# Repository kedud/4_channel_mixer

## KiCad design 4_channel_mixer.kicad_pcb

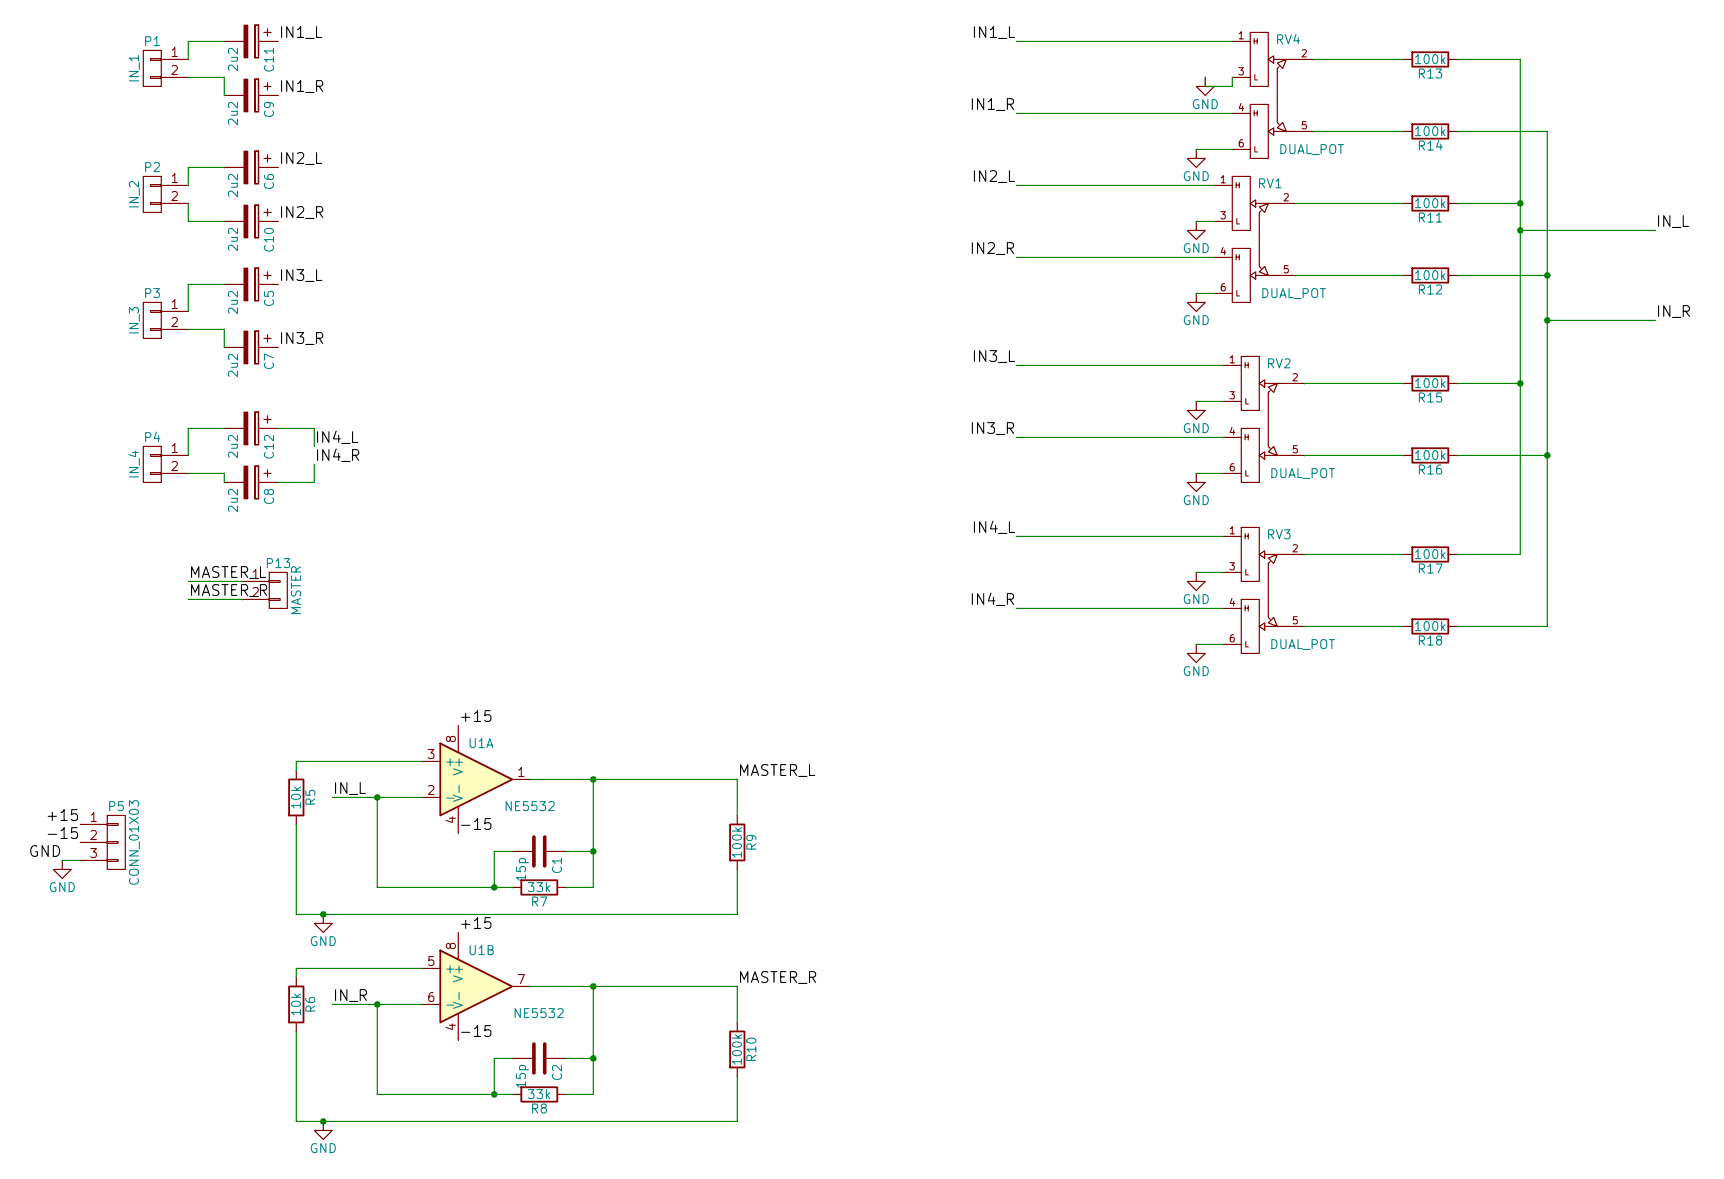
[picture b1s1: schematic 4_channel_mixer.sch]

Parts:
C1, C2: 15p; C_Disc_D3_P2.5
C5, C6, C7, C8, C9, C10, C11, C12: 2u2; C_Radial_D5_L11_P2.5
P1: IN_1; Pin_Header_Angled_1x02
P2: IN_2; Pin_Header_Angled_1x02
P3: IN_3; Pin_Header_Angled_1x02
P4: IN_4; Pin_Header_Angled_1x02
P5: CONN_01X03; Pin_Header_Angled_1x03
P13: MASTER; Pin_Header_Angled_1x02
R5, R6: 10k; Resistor_Horizontal_RM15mm
R7, R8: 33k; Resistor_Horizontal_RM15mm
R9, R10, R11, R12, R13, R14, R15, R16, R17, R18: 100k; Resistor_Horizontal_RM15mm
RV1, RV2, RV3, RV4: DUAL_POT; Potentiometer_ALPS_RK27112A0A16
U1: NE5532; DIP_8

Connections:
/+15: P5.1, U1.8 (V+)
/-15: P5.2, U1.4 (V-)
/IN1_L: C11.1, RV4.1
/IN1_R: C9.1, RV4.4
/IN2_L: C6.1, RV1.1
/IN2_R: C10.1, RV1.4
/IN3_L: C5.1, RV2.1
/IN3_R: C7.1, RV2.4
/IN4_L: C12.1, RV3.1
/IN4_R: C8.1, RV3.4
/IN_L: C1.2, R7.2, R11.1, R13.1, R15.1, R17.1, U1.2 (-)
/IN_R: C2.2, R8.2, R12.1, R14.1, R16.1, R18.1, U1.6 (-)
/MASTER_L: C1.1, P13.1, R7.1, R9.1, U1.1
/MASTER_R: C2.1, P13.2, R8.1, R10.1, U1.7
GND: P5.3, R5.2, R6.2, R9.2, R10.2, RV1.3, RV1.6, RV2.3, RV2.6, RV3.3, RV3.6, RV4.3, RV4.6
unnamed: C5.2, P3.1
unnamed: C6.2, P2.1
unnamed: C7.2, P3.2
unnamed: C8.2, P4.2
unnamed: C9.2, P1.2
unnamed: C10.2, P2.2
unnamed: C11.2, P1.1
unnamed: C12.2, P4.1
unnamed: R5.1, U1.3 (+)
unnamed: R6.1, U1.5 (+)
unnamed: R11.2, RV1.2
unnamed: R12.2, RV1.5
unnamed: R13.2, RV4.2
unnamed: R14.2, RV4.5
unnamed: R15.2, RV2.2
unnamed: R16.2, RV2.5
unnamed: R17.2, RV3.2
unnamed: R18.2, RV3.5

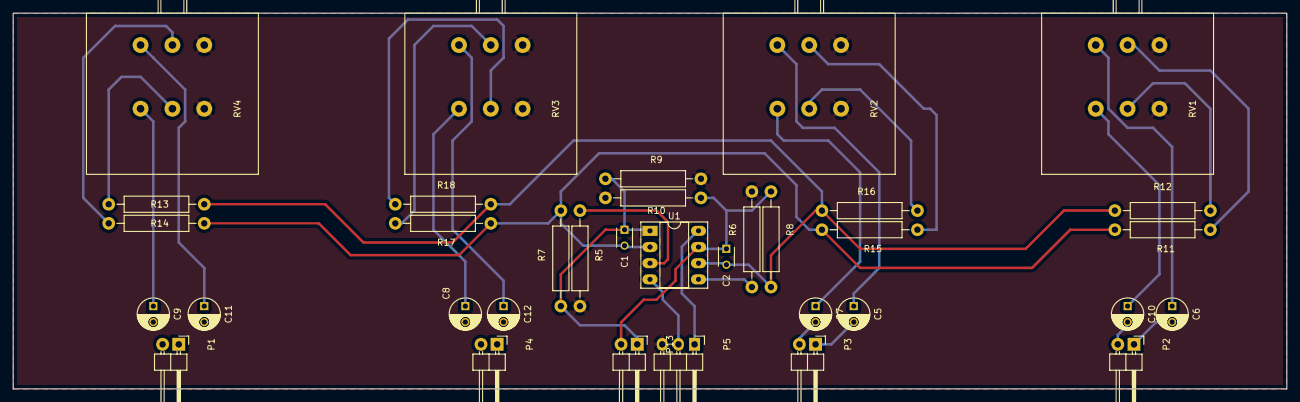
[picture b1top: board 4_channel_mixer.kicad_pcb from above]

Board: 2 copper layers, 200.0 x 59.0 mm, 35 parts (0 on the bottom side), 33 nets.
